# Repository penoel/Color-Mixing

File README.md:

# Color-Mixing
This is a simple color mixing electronics kit.  It uses a potentiometer to change the voltage (simple voltage divider) on a RGB LED. This is done for the red, green, and blue.  These voltages also go to a single RGB LED that shows the mixing. The three colors require different amounts of power for the same intensity, so choose your resistor accordingly.

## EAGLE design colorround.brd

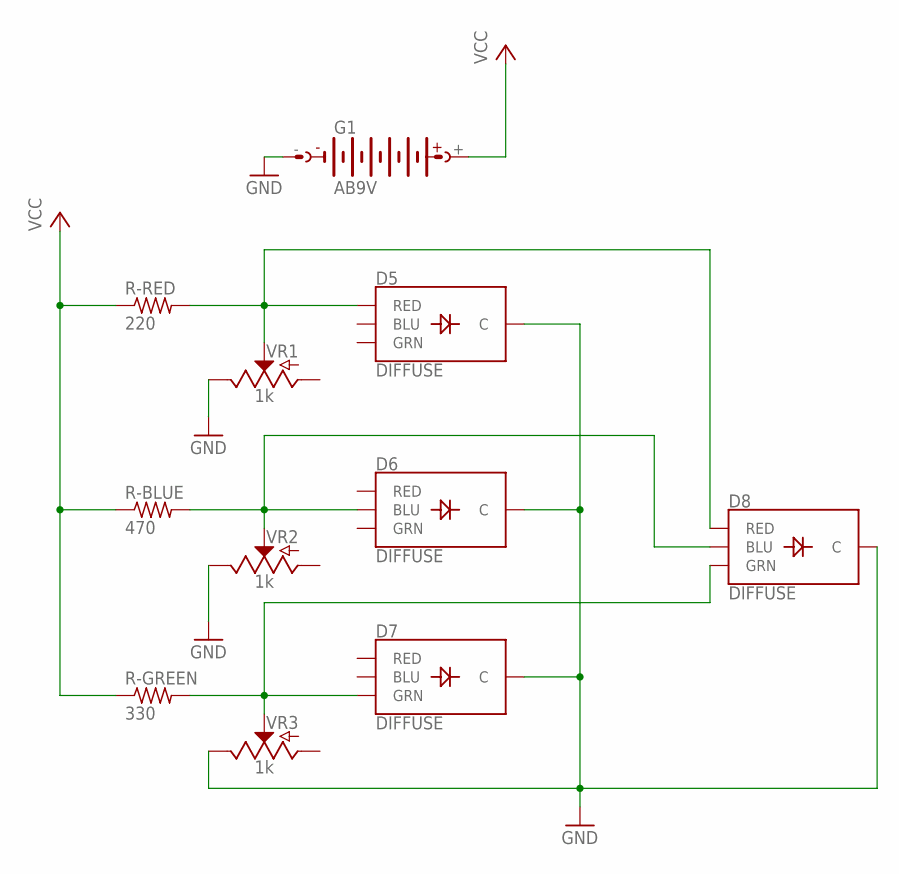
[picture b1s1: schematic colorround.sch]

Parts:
D5, D6, D7, D8: DIFFUSE; LED-RGB-THRU
G1: AB9V
R-BLUE: 470; 0207/10
R-GREEN: 330; 0207/10
R-RED: 220; 0207/10
VR1, VR2, VR3: 1k; POT-PTH-ALPS

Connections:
GND: D5.2 (C), D6.2 (C), D7.2 (C), D8.2 (C), G1.-, VR1.P$1 (E), VR2.P$1 (E), VR3.P$1 (E)
unnamed: D5.1 (RED), D8.1 (RED), R-RED.2, VR1.P$2 (S)
unnamed: D6.4 (BLU), D8.4 (BLU), R-BLUE.2, VR2.P$2 (S)
unnamed: D7.3 (GRN), D8.3 (GRN), R-GREEN.2, VR3.P$2 (S)
VCC: G1.+, R-BLUE.1, R-GREEN.1, R-RED.1

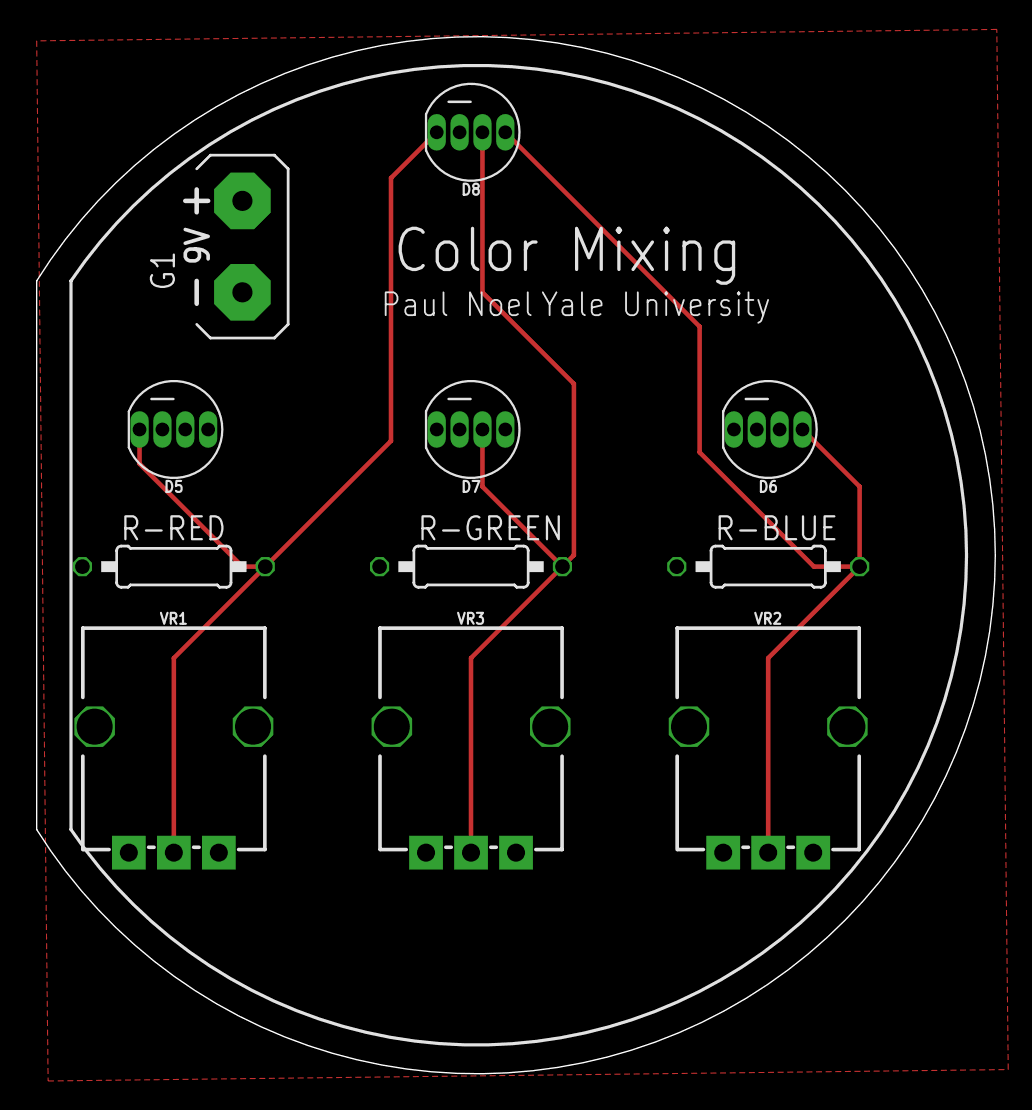
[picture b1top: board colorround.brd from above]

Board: 2 copper layers, 53.3 x 57.6 mm, 11 parts (0 on the bottom side), 5 nets.

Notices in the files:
parts and their libraries:
SparkFun-LED: Licensing: Creative Commons ShareAlike 4.0 International - https://creativecommons.org/licenses/by-sa/4.0
